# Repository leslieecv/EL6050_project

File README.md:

# Proyecto de curso EL6050

- Leslie Cárdenas
- Nicolás Ruminot

Link de repositorio:  

[https://github.com/leslieecv/EL6050_project.git](https://github.com/leslieecv/EL6050_project.git)

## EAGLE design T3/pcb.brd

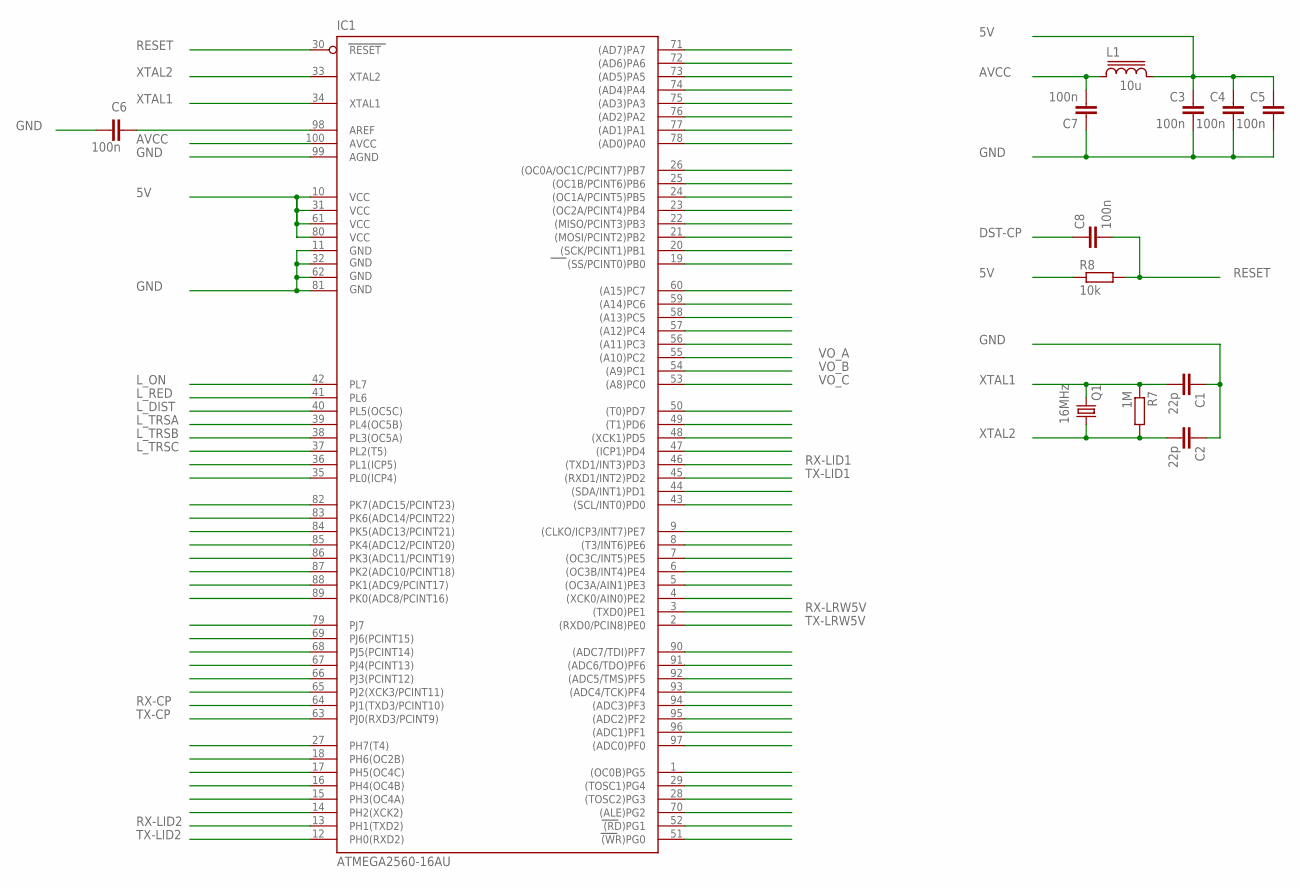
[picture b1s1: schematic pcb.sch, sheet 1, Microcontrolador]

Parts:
C1, C2: 22p; C050-025X075
C3, C4, C5, C6, C7, C8: 100n; C050-025X075
IC1: ATMEGA2560-16AU; TQFP100
L1: 10u; MSS1260
Q1: 16MHz; HC18U-V
R7: 1M; R1206W
R8: 10k; R1206W

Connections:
5V: C3.2, C4.2, C5.2, IC1.10 (VCC), IC1.31 (VCC1), IC1.61 (VCC2), IC1.80 (VCC3), L1.2, R8.1; also elsewhere on the board
AVCC: C7.2, IC1.100 (AVCC), L1.1
DST-CP: C8.1; also elsewhere on the board
GND: C1.1, C2.1, C3.1, C4.1, C5.1, C6.2, C7.1, IC1.11 (GND), IC1.32 (GND1), IC1.62 (GND2), IC1.81 (GND3), IC1.99 (AGND); also elsewhere on the board
L_DIST: IC1.40 (PL5(OC5C)); also elsewhere on the board
L_ON: IC1.42 (PL7); also elsewhere on the board
L_RED: IC1.41 (PL6); also elsewhere on the board
L_TRSA: IC1.39 (PL4(OC5B)); also elsewhere on the board
L_TRSB: IC1.38 (PL3(OC5A)); also elsewhere on the board
L_TRSC: IC1.37 (PL2(T5)); also elsewhere on the board
unnamed: C6.1, IC1.98 (AREF)
RESET: C8.2, IC1.30 (RESET), R8.2
RX-CP: IC1.64 (PJ1(TXD3/PCINT10)); also elsewhere on the board
RX-LID1: IC1.46 ((TXD1/INT3)PD3); also elsewhere on the board
RX-LID2: IC1.13 (PH1(TXD2)); also elsewhere on the board
RX-LRW5V: IC1.3 ((TXD0)PE1); also elsewhere on the board
TX-CP: IC1.63 (PJ0(RXD3/PCINT9)); also elsewhere on the board
TX-LID1: IC1.45 ((RXD1/INT2)PD2); also elsewhere on the board
TX-LID2: IC1.12 (PH0(RXD2)); also elsewhere on the board
TX-LRW5V: IC1.2 ((RXD0/PCIN8)PE0); also elsewhere on the board
VO_A: IC1.55 ((A10)PC2); also elsewhere on the board
VO_B: IC1.54 ((A9)PC1); also elsewhere on the board
VO_C: IC1.53 ((A8)PC0); also elsewhere on the board
XTAL1: C1.2, IC1.34 (XTAL1), Q1.1, R7.1
XTAL2: C2.2, IC1.33 (XTAL2), Q1.2, R7.2

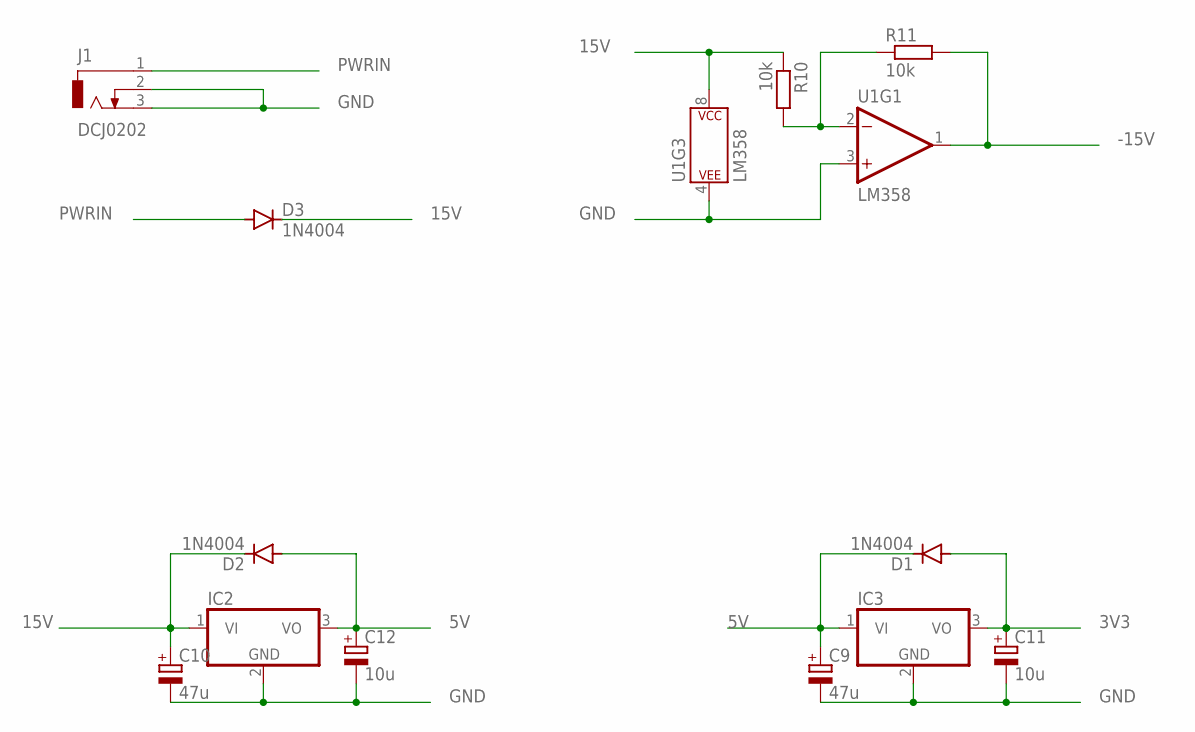
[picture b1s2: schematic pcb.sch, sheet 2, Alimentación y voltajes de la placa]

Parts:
C9, C10: 47u; E2,5-6E
C11, C12: 10u; E2,5-6E
D1, D2, D3: 1N4004; DO41-10
IC2, IC3: 7805T; TO220H
J1: DCJ0202
R10, R11: 10k; R1206W
U1: LM358; DIP08

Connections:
3V3: C11.+, D1.A, IC3.3 (VO); also elsewhere on the board
5V: C9.+, C12.+, D1.C, D2.A, IC2.3 (VO), IC3.1 (VI); also elsewhere on the board
15V: C10.+, D2.C, D3.C, IC2.1 (VI), R10.1, U1.8 (P$V+); also elsewhere on the board
-15V: R11.2, U1.1 (OUT); also elsewhere on the board
GND: C9.-, C10.-, C11.-, C12.-, IC2.2 (GND), IC3.2 (GND), J1.2, J1.3, U1.3 (+IN), U1.4 (P$V-); also elsewhere on the board
unnamed: R10.2, R11.1, U1.2 (-IN)
PWRIN: D3.A, J1.1

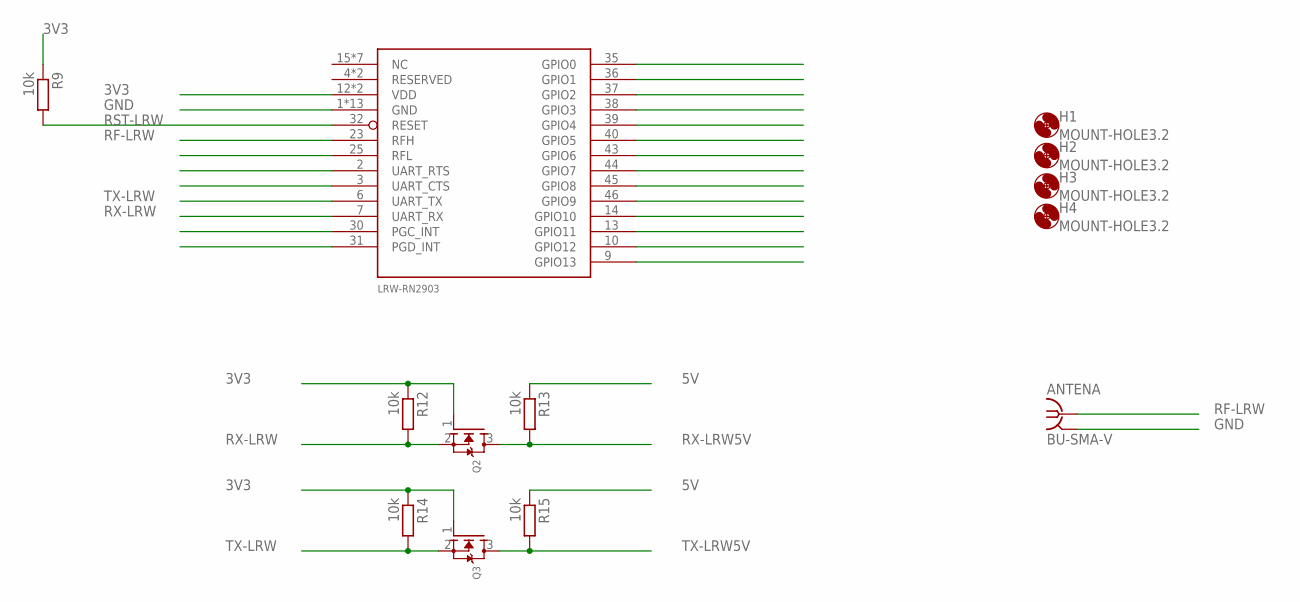
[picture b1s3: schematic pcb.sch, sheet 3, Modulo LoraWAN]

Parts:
ANTENA: BU-SMA-V
H1, H2, H3, H4: MOUNT-HOLE3.2; 3,2
LRW-RN2903: MICROCHIP_RN2483
Q2, Q3: MOSFET-NWAVE; SOT23-W
R9, R12, R13, R14, R15: 10k; R1206W

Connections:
3V3: LRW-RN2903.12 (VDD), LRW-RN2903.34 (VDD), Q2.1 (G), Q3.1 (G), R9.1, R12.1, R14.1; also elsewhere on the board
5V: R13.1, R15.1; also elsewhere on the board
GND: ANTENA.2, ANTENA.3 (2), ANTENA.4 (2), ANTENA.5 (2), LRW-RN2903.1 (GND), LRW-RN2903.8 (GND), LRW-RN2903.11 (GND), LRW-RN2903.20 (GND), LRW-RN2903.21 (GND), LRW-RN2903.22 (GND), LRW-RN2903.24 (GND), LRW-RN2903.26 (GND), LRW-RN2903.27 (GND), LRW-RN2903.28 (GND), LRW-RN2903.33 (GND), LRW-RN2903.41 (GND), LRW-RN2903.47 (GND); also elsewhere on the board
RF-LRW: ANTENA.1, LRW-RN2903.23 (RFH)
RST-LRW: LRW-RN2903.32 (RESET), R9.2
RX-LRW: LRW-RN2903.7 (UART_RX), Q2.2 (S), R12.2
RX-LRW5V: Q2.3 (D), R13.2; also elsewhere on the board
TX-LRW: LRW-RN2903.6 (UART_TX), Q3.2 (S), R14.2
TX-LRW5V: Q3.3 (D), R15.2; also elsewhere on the board

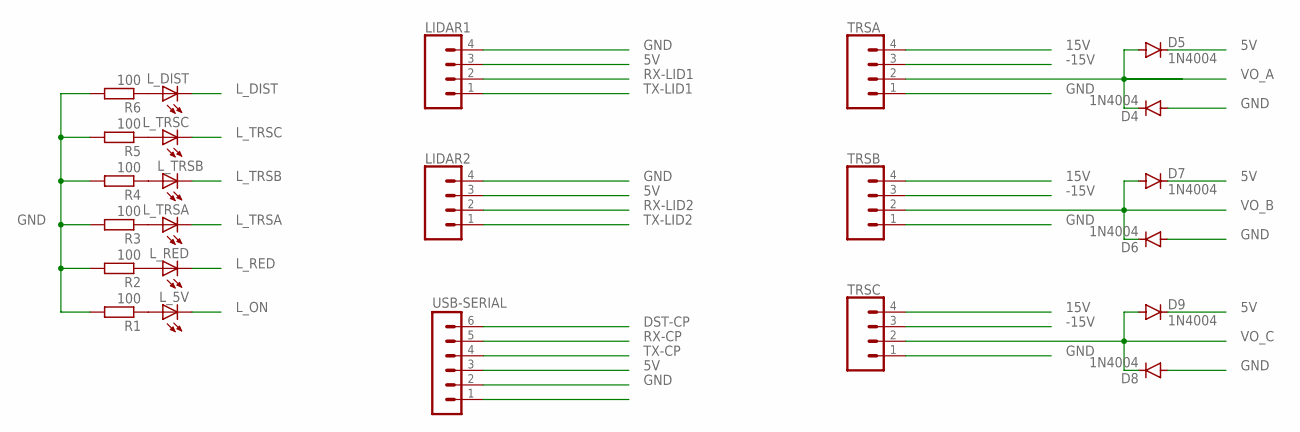
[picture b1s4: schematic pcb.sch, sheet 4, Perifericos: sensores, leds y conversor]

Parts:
D4, D5, D6, D7, D8, D9: 1N4004; DO41-10
LIDAR1, LIDAR2: CONN_04JST-PTH; JST-4-PTH
L_5V: LED5MM
L_DIST: LED5MM
L_RED: LED5MM
L_TRSA: LED5MM
L_TRSB: LED5MM
L_TRSC: LED5MM
R1, R2, R3, R4, R5, R6: 100; R1206W
TRSA: CONN_04JST-PTH; JST-4-PTH
TRSB: CONN_04JST-PTH; JST-4-PTH
TRSC: CONN_04JST-PTH; JST-4-PTH
USB-SERIAL: MA06-1

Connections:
5V: D5.C, D7.C, D9.C, LIDAR1.3, LIDAR2.3, USB-SERIAL.3; also elsewhere on the board
15V: TRSA.4, TRSB.4, TRSC.4; also elsewhere on the board
-15V: TRSA.3, TRSB.3, TRSC.3; also elsewhere on the board
DST-CP: USB-SERIAL.6; also elsewhere on the board
GND: D4.A, D6.A, D8.A, LIDAR1.4, LIDAR2.4, R1.2, R2.2, R3.2, R4.2, R5.2, R6.2, TRSA.1, TRSB.1, TRSC.1, USB-SERIAL.2; also elsewhere on the board
L_DIST: L_DIST.K (C); also elsewhere on the board
L_ON: L_5V.K (C); also elsewhere on the board
L_RED: L_RED.K (C); also elsewhere on the board
L_TRSA: L_TRSA.K (C); also elsewhere on the board
L_TRSB: L_TRSB.K (C); also elsewhere on the board
L_TRSC: L_TRSC.K (C); also elsewhere on the board
unnamed: L_TRSB.A, R4.1
unnamed: L_5V.A, R1.1
unnamed: L_RED.A, R2.1
unnamed: L_TRSA.A, R3.1
unnamed: L_TRSC.A, R5.1
unnamed: L_DIST.A, R6.1
RX-CP: USB-SERIAL.5; also elsewhere on the board
RX-LID1: LIDAR1.2; also elsewhere on the board
RX-LID2: LIDAR2.2; also elsewhere on the board
TX-CP: USB-SERIAL.4; also elsewhere on the board
TX-LID1: LIDAR1.1; also elsewhere on the board
TX-LID2: LIDAR2.1; also elsewhere on the board
VO_A: D4.C, D5.A, TRSA.2; also elsewhere on the board
VO_B: D6.C, D7.A, TRSB.2; also elsewhere on the board
VO_C: D8.C, D9.A, TRSC.2; also elsewhere on the board

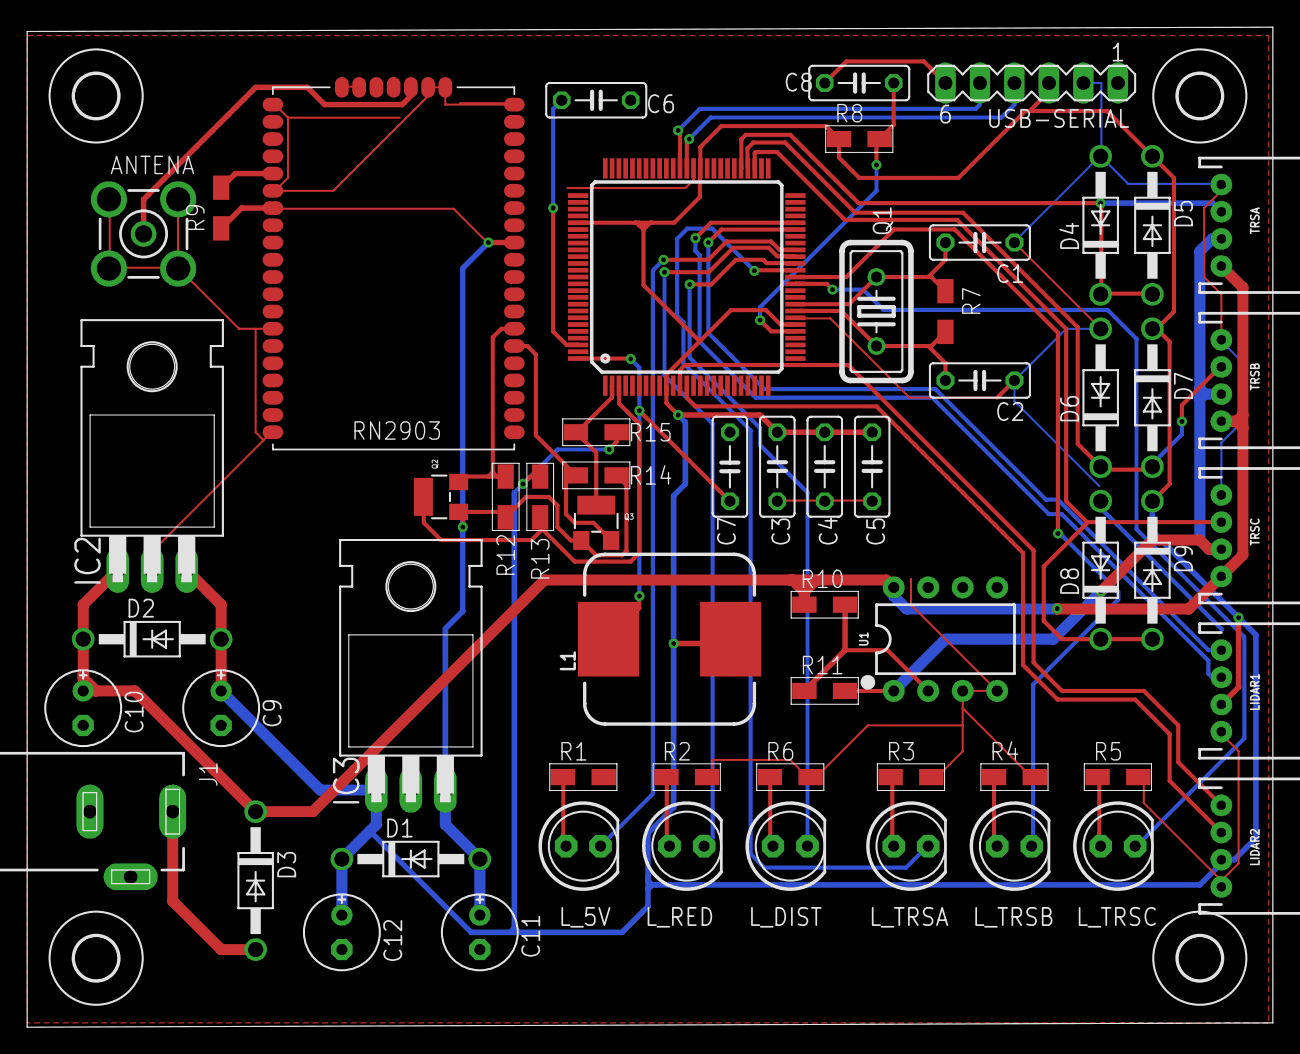
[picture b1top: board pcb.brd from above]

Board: 2 copper layers, 91.7 x 73.6 mm, 63 parts (0 on the bottom side), 40 nets.

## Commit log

2023-05-30 add lorawan module and arduino to schematic
2023-06-09 add and connect components
2023-06-22 all components added and board started
2023-06-26 end board and update schematic
2023-06-30 hardware complete
2023-06-30 start main and lidar related code
2023-06-30 update lidar state machine
2023-06-30 update files
2023-07-01 update files, add comments
2023-07-03 Update main.ino
    agregue libreria eeprom para guardar errores en la memoria no volatil
2023-07-04 update lidar
2023-07-04 update code
2023-07-12 add all files
2023-07-12 add images
2023-07-12 add presentation slides
2023-07-14 move files
2023-07-14 move file

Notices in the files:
parts and their libraries:
sparkfun-connectors: Licensing: Creative Commons ShareAlike 4.0 International - https://creativecommons.org/licenses/by-sa/4.0
